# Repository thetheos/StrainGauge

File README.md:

View this project on [CADLAB.io](https://cadlab.io/project/1158). 

# StrainGauge

Here is a proto shield for arduino uno to easily mount strain gauges. It uses the pin A1 to read the output of the instrumental
amp (ina125p).

I wrote also a small program wich can read the input of the signal on pin A1 and rewrite it on the serial monnitor (9600 baud). 
There is 2 mode of reading:
-Continuous reading (read in continuous...)
-Triger mode read: print data only when the strain gage is stressed. The triger mode settings can be modified in the program via serial
monitor (both the sensitivity of the triger and the sample rate).

This project was designed to measure the thrust power of a propellant motor.

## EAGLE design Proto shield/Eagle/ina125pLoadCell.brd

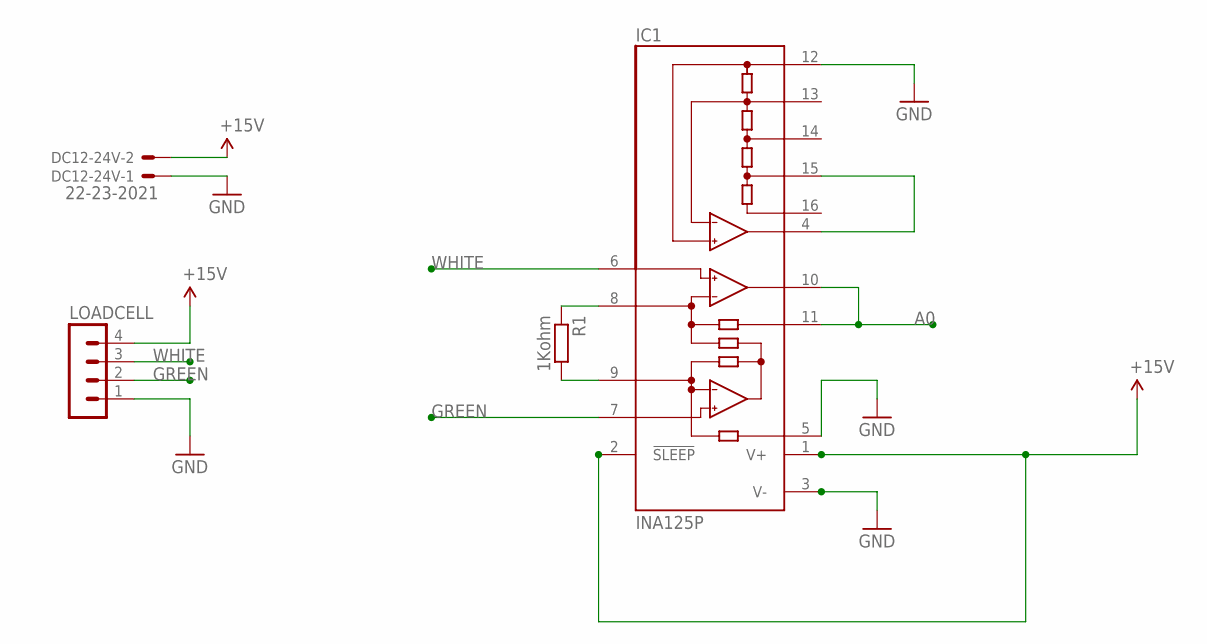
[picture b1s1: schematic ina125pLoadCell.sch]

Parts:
DC12-24V: 22-23-2021
IC1: INA125P; DIL16
LOADCELL: MA04-1
R1: 1Kohm; 0207/7

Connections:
+15V: IC1.1 (V+), IC1.2 (!SLEEP)
A0: IC1.10 (OUT), IC1.11 (SENSE)
AREF: IC1.4 (REFOUT), IC1.15 (REF5)
GND: DC12-24V.1, IC1.3 (V-), IC1.5 (REF), IC1.12 (REFCOM), LOADCELL.1
GREEN: IC1.7 (-IN), LOADCELL.2
unnamed: IC1.9 (RG), R1.2
unnamed: IC1.8 (RG), R1.1
VCC: DC12-24V.2, LOADCELL.4
WHITE: IC1.6 (+IN), LOADCELL.3

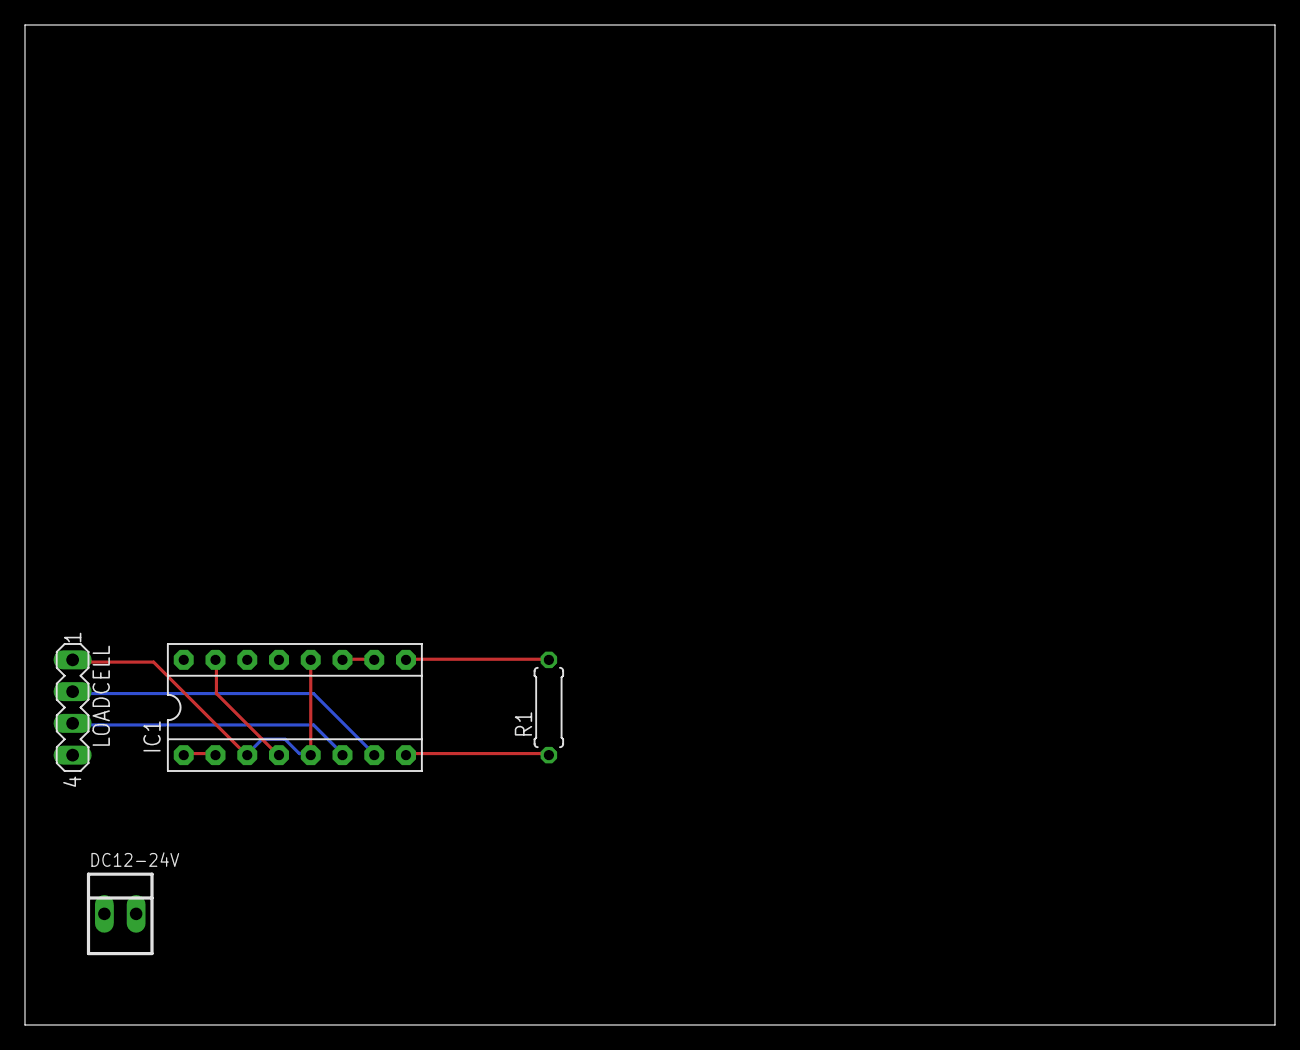
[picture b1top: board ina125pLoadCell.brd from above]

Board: 2 copper layers, 100.0 x 80.0 mm, 4 parts (0 on the bottom side), 9 nets.

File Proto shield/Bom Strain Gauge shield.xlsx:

pièce | quantité | prix | lien
S type strain gauge 100kg | 1 | 25.02 | https://www.aliexpress.com/item/strain-gauge-pressure-sensor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
Ina125p instrumentation amp | 5 | 14.44 | https://www.aliexpress.com/item/FREE-SHIPPING-INA125P-INA125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
arduino uno | 1 | 3.52 | https://www.aliexpress.com/item/2014-The-new-Ard-uino-UNO-R3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
trimpot 1Kohm | 45 | 4.8600000000000003 | https://www.aliexpress.com/snapshot/0.html?orderId=849487779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

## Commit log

2017-07-03 initial
2017-07-06 add time and delay setting plus bug correction/
2017-07-09 new test in data logger begin of a plotter/
2017-07-11 more useable plotter/
2017-07-15 improving design/
2017-07-20 Serial port selection add
2017-07-21 Add logger, reset button, solve multiple bug, enlarge TODO list
2017-07-22 Add a checbox to log data file
2017-07-26 Add files via upload
    class test
2017-07-31 Add files via upload
    class
2018-06-10 Backlink to CADLAB.io has been added.

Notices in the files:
parts and their libraries:
SparkFun-Aesthetics: Licensing: Creative Commons ShareAlike 4.0 International - https://creativecommons.org/licenses/by-sa/4.0
